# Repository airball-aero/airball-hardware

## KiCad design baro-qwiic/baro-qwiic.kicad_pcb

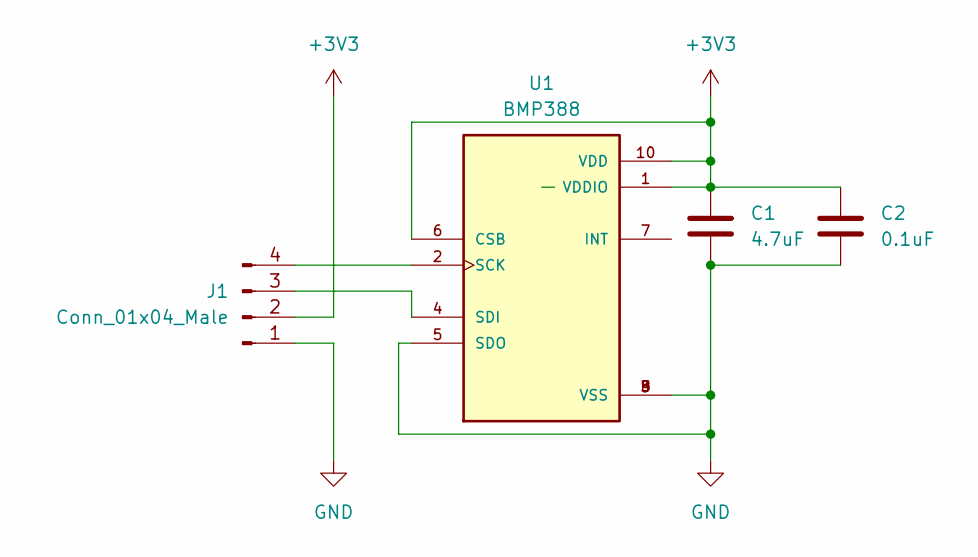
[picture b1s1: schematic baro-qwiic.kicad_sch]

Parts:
C1: 4.7uF; C_0603_1608Metric
C2: 0.1uF; C_0603_1608Metric
J1: Conn_01x04_Male; JST_SH_BM04B-SRSS-TB_1x04-1MP_P1.00mm_Vertical
U1: BMP388; PARTREV 1.1

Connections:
+3V3: C1.1, C2.1, J1.2, U1.1 (VDDIO), U1.6 (CSB), U1.10 (VDD)
GND: C1.2, C2.2, J1.1, U1.3 (VSS), U1.5 (SDO), U1.8 (VSS), U1.9 (VSS)
unnamed: J1.3, U1.4 (SDI)
unnamed: J1.4, U1.2 (SCK)

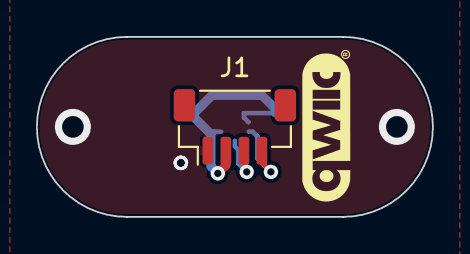
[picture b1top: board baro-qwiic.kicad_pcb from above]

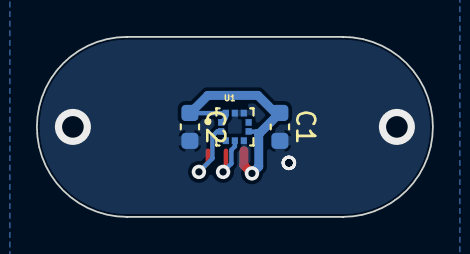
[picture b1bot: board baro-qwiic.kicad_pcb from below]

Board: 2 copper layers, 22.0 x 10.0 mm, 4 parts (3 on the bottom side), 4 nets.

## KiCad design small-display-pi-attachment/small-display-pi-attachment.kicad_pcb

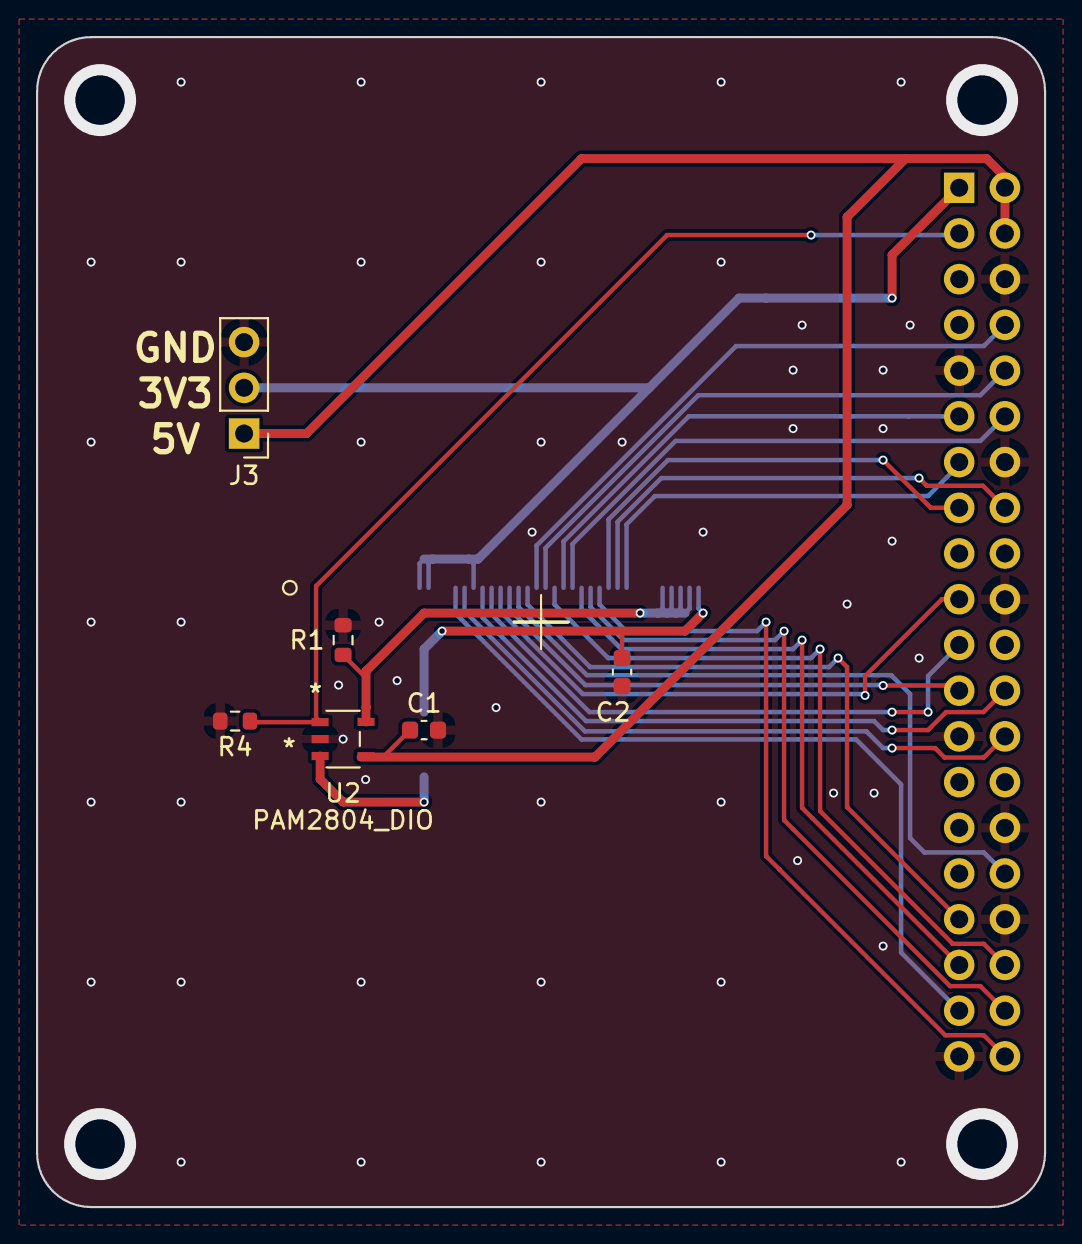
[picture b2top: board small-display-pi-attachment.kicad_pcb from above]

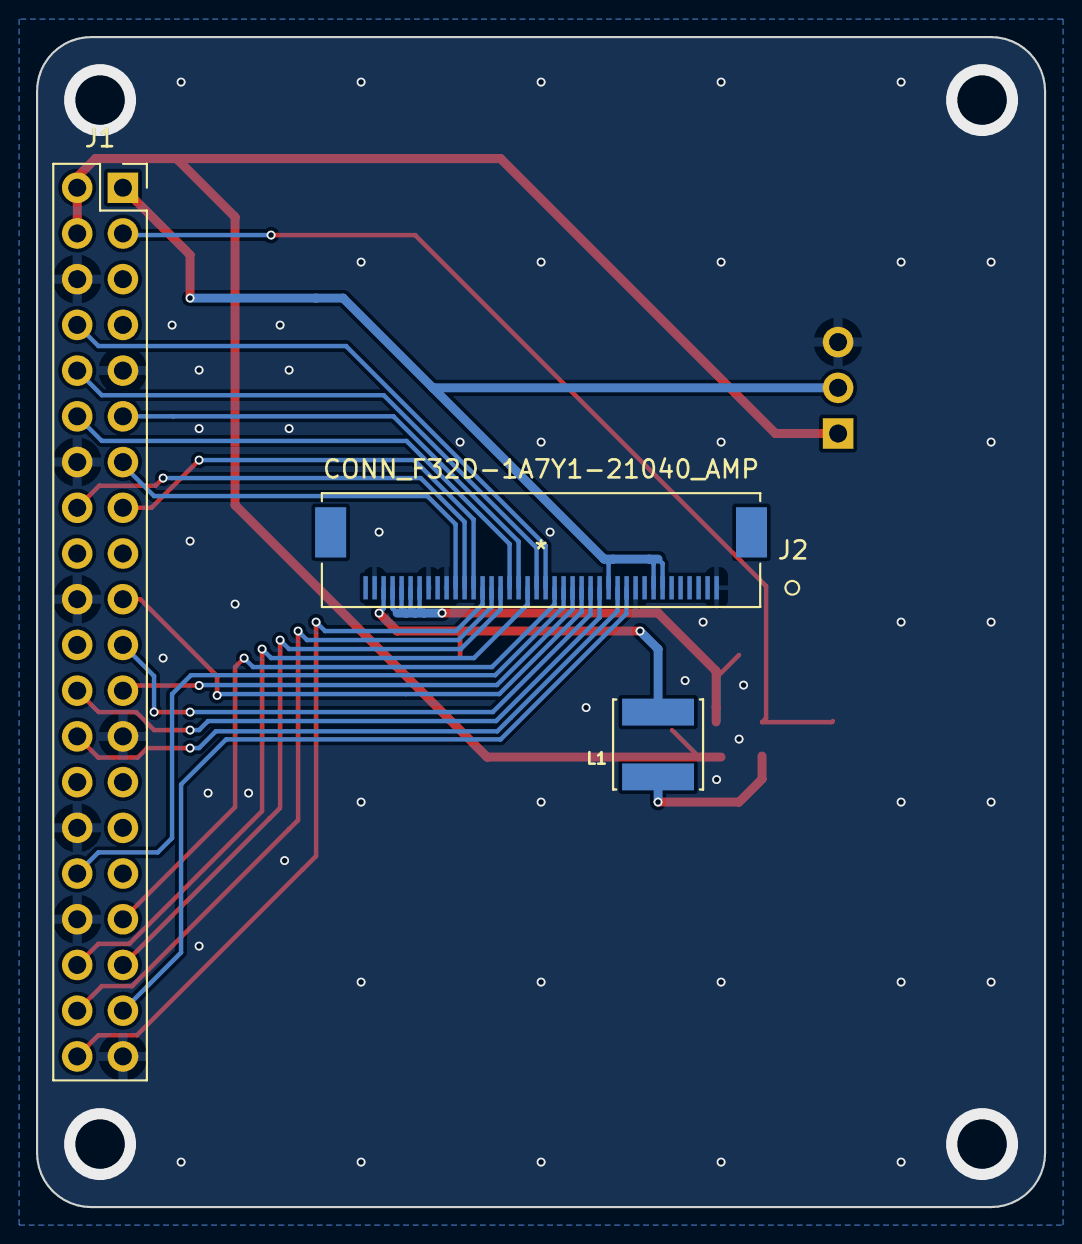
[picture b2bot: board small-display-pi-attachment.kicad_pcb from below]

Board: 2 copper layers, 56.0 x 65.0 mm, 9 parts (3 on the bottom side), 26 nets.

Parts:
C1, C2: 10 uF; C_0603_1608Metric
J1: Conn_01x40; PinSocket_2x20_P2.54mm_Vertical
J2: CONN_F32D-1A7Y1-21040_AMP; F32D-1A7Y1-21040
J3: Conn_01x03; PinHeader_1x03_P2.54mm_Vertical
L1: 4.7 uH; IND_VLS5045EX-100M
R1: 1 Ω; R_0603_1608Metric
R4: 10k; R_0603_1608Metric
U2: PAM2804_DIO; PAM2804AAB010

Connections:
+3V3: J1.1, J2.7, J2.8, J2.13, J3.2
+5V: C1.1, J1.2, J1.4, J3.1, U2.4 (VIN)
/!RESET: J1.13, J2.30
/!WRITE: J1.26, J2.12
/DAT_CMD: J1.37, J2.11
/DB0: J1.24, J2.14
/DB1: J1.21, J2.15
/DB2: J1.19, J2.16
/DB3: J1.23, J2.17
/DB4: J1.32, J2.18
/DB5: J1.33, J2.19
/DB6: J1.8, J2.20
/DB7: J1.10, J2.21
/DB8: J1.36, J2.22
/DB9: J1.11, J2.23
/DB10: J1.12, J2.24
/DB11: J1.35, J2.25
/DB12: J1.38, J2.26
/DB13: J1.40, J2.27
/DB14: J1.15, J2.28
/DB15: J1.16, J2.29
/LED_A: C2.1, J2.38, L1.2
/LED_K: J2.34, J2.35, J2.36, J2.37, R1.1, U2.5 (FB)
/PWM: J1.3, R4.1, U2.1 (EN)
GND: C1.2, C2.2, J1.6, J1.9, J1.14, J1.20, J1.25, J1.30, J1.34, J1.39, J2.1, J2.10, J2.31, J2.33, J2.39, J3.3, R1.2, R4.2, U2.2 (GND)
unnamed: L1.1, U2.3 (SW)

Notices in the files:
parts and their libraries:
Copyright 2021 Accelerated Designs. All rights reserved.
